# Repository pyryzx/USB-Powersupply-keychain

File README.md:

# Multi-Rail Power Supply Keychain (USB-C PD)

A compact, keychain-sized **USB-C powered** power supply that has four power rails:

- **+1.8 V** (up to 1.5 A)
- **+3.3 V** (up to 1.5 A)
- **+5 V** (up to 1.5 A)
- **+12 V (VBUS passthrough)** from the USB-C PD source

Clip this onto your keys, plug it into a USB-C PD charger, and you’ve got the most common lab voltages available from a single tiny board.

---

## Features

- USB-C input with **USB Power Delivery negotiation** (requests 12 V from a capable source)
- Multi-rail DC/DC conversion to generate **1.8 V, 3.3 V, and 5 V**
- **12 V VBUS rail is also available** as an output (source-dependent)
- Compact PCB with **keychain hole**

---

## Electrical Specs (Target)

> Real limits depend heavily on the USB-C PD source, total load, copper/thermal conditions, and airflow.

### Outputs

| Rail | Nominal Voltage | Max Current (design target) | Notes |
|---|---:|---:|---|
| +1.8V | 1.8 V | 1.5 A | Buck regulated |
| +3.3V | 3.3 V | 1.5 A | Buck regulated |
| +5V | 5.0 V | 1.5 A | Buck regulated |
| +12V | 12 V | Source-dependent | Direct from negotiated VBUS |

### Power Budget 

beware that even if each rail is “rated” for 1.5 A it is source dependent. 

Example (typical PD): **12 V × 3 A = 36 W available**  
Loads:
- 5 V @ 1.5 A ≈ 7.5 W  
- 3.3 V @ 1.5 A ≈ 5.0 W  
- 1.8 V @ 1.5 A ≈ 2.7 W  
Total ≈ 15.2 W (plus conversion losses)

Beware that current design is not yet optimized to be run at full capacity all the time. Heat generated is still a problem when run at max load.

## Output Connector / Pinout

### J3

Pin order (as labeled on schematic / silkscreen intent):

1. **+1.8V**
2. **+3.3V**
3. **+5V**
4. **+12V**
5. **GND**

---

## How It Works 

1. **USB-C input** comes in on the Type-C receptacle.
2. A **USB-C PD sink controller (CYPD3177-24LQ)** negotiates with the charger to request **12 V** output.
3. Once VBUS is valid, a small input switching/protection stage connects the negotiated rail to the board.
4. A **multi-output buck regulator (TPS65581PWP)** generates:
   - **1.8 V** (via L1)
   - **3.3 V** (via L2)
   - **5 V** (via L3)
5. The negotiated **+12 V VBUS** rail is also routed to the output header.

See: `schematic_keychain V2.pdf`. :contentReference[oaicite:1]{index=1}

---

## What This Is For

- Powering sensors, dev boards, and small embedded prototypes
- Quick “bench supply” substitute for field work
- Testing boards that need 1.8 V / 3.3 V / 5 V without dragging a lab PSU around

---

## What This Is NOT For

- Not a charger / power bank
- Not safety-certified equipment
- Not intended for life-critical, medical, automotive, or mains-related applications
- Not meant for inductive loads / motors directly 

---

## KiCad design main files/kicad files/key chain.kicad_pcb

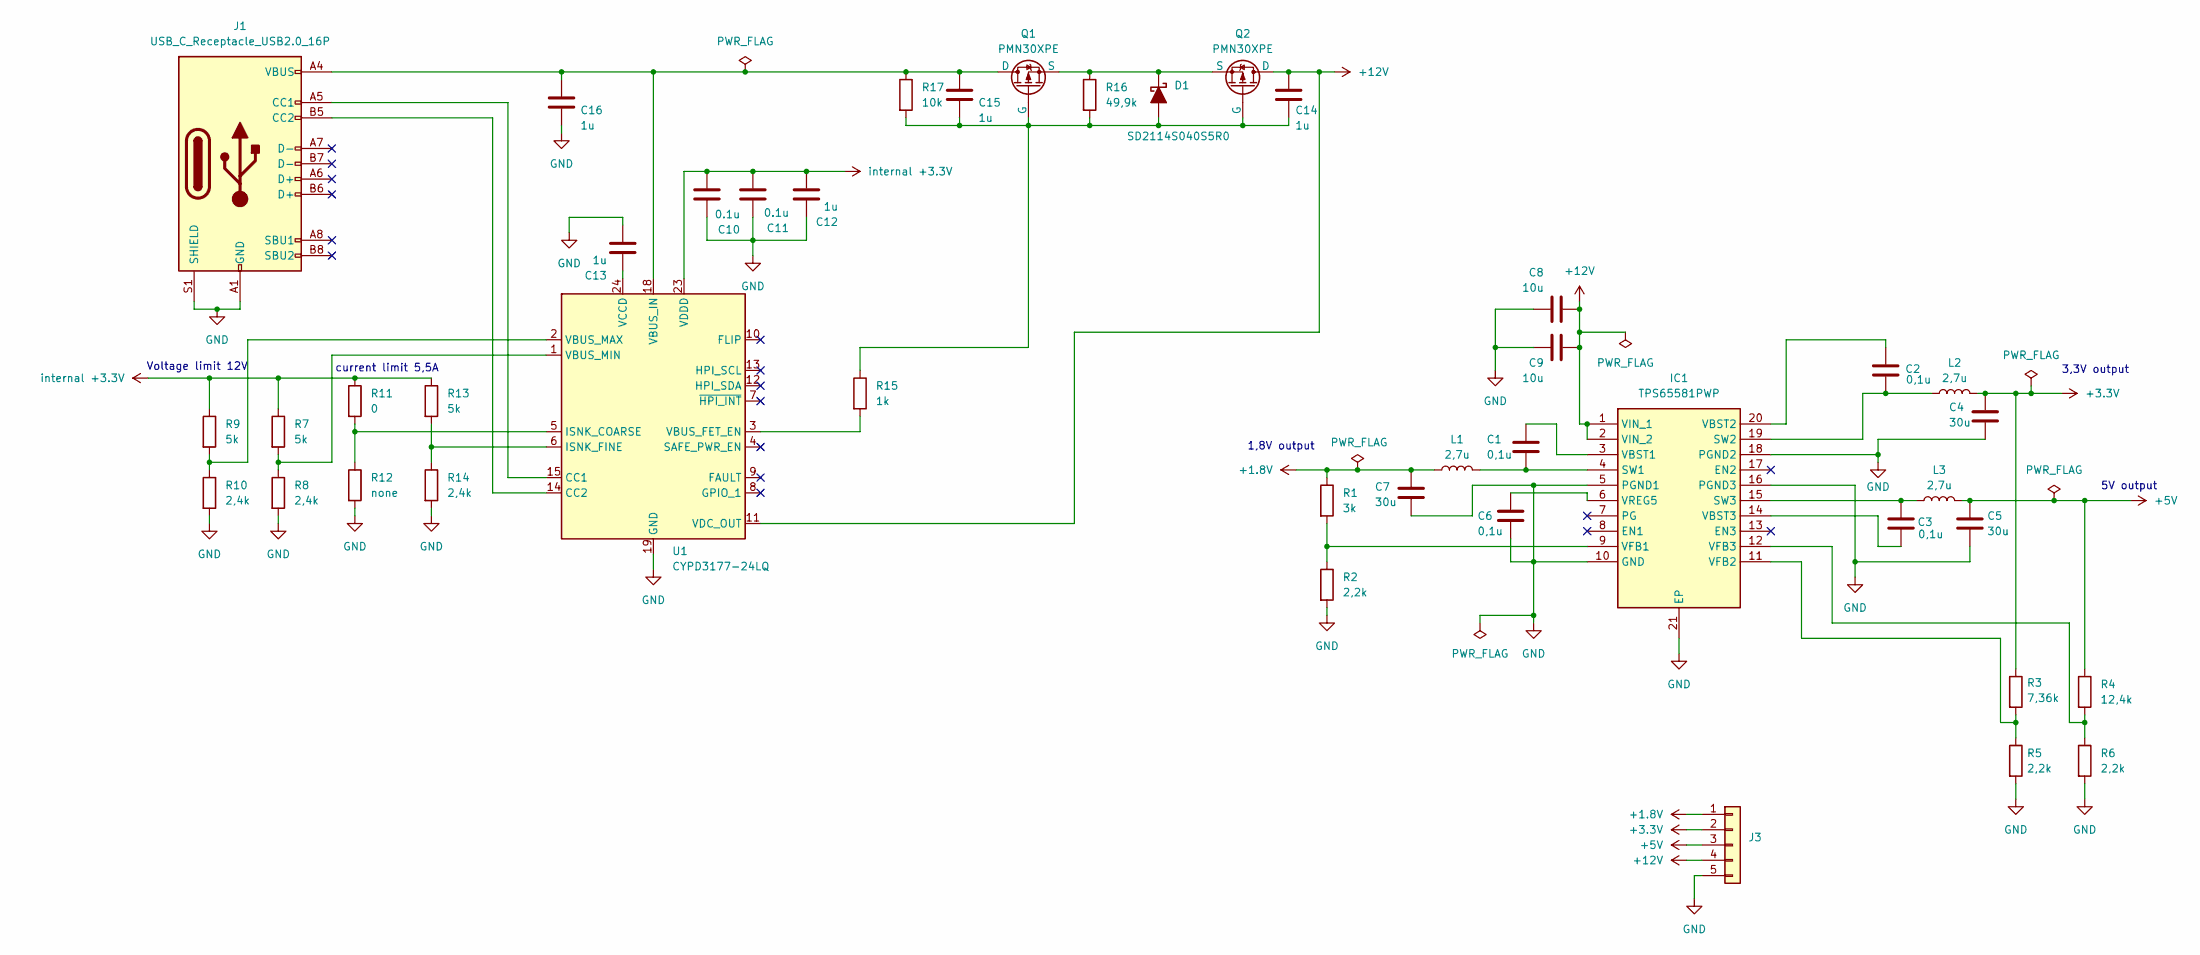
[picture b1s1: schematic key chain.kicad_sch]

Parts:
C1, C2, C3, C6: 0,1u; C_0603_1608Metric_Pad1.08x0.95mm_HandSolder
C4, C5, C7: 30u; C_0603_1608Metric_Pad1.08x0.95mm_HandSolder
C8, C9: 10u; C_0603_1608Metric_Pad1.08x0.95mm_HandSolder
C10, C11: 0.1u; C_0603_1608Metric_Pad1.08x0.95mm_HandSolder
C12, C13, C14, C15, C16: 1u; C_0603_1608Metric_Pad1.08x0.95mm_HandSolder
D1: SD2114S040S5R0
IC1: TPS65581PWP; SOP65P640X120-21N; Mouser Part Number 595-TPS65581PWP
J1: USB_C_Receptacle_USB2.0_16P; USB_C_Receptacle_HRO_TYPE-C-31-M-12
J3: Conn_01x05; PinSocket_1x05_P2.54mm_Vertical
L1, L2, L3: 2,7u; L_1812_4532Metric_Pad1.30x3.40mm_HandSolder
Q1, Q2: PMN30XPE; TSOP-6_1.65x3.05mm_P0.95mm
R1: 3k; R_0603_1608Metric_Pad0.98x0.95mm_HandSolder
R2, R5, R6: 2,2k; R_0603_1608Metric_Pad0.98x0.95mm_HandSolder
R3: 7,36k; R_0603_1608Metric_Pad0.98x0.95mm_HandSolder
R4: 12,4k; R_0603_1608Metric_Pad0.98x0.95mm_HandSolder
R7, R9, R13: 5k; R_0603_1608Metric_Pad0.98x0.95mm_HandSolder
R8, R10, R14: 2,4k; R_0603_1608Metric_Pad0.98x0.95mm_HandSolder
R11: 0; R_0603_1608Metric_Pad0.98x0.95mm_HandSolder
R12: none; R_0603_1608Metric_Pad0.98x0.95mm_HandSolder
R15: 1k; R_0603_1608Metric_Pad0.98x0.95mm_HandSolder
R16: 49,9k; R_0603_1608Metric_Pad0.98x0.95mm_HandSolder
R17: 10k; R_0603_1608Metric_Pad0.98x0.95mm_HandSolder
U1: CYPD3177-24LQ; QFN-24-1EP_4x4mm_P0.5mm_EP2.75x2.75mm

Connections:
+1.8V: C7.1, J3.1, L1.1, R1.1
+3.3V: C4.1, J3.2, L2.2, R3.1
+5V: C5.1, J3.3, L3.2, R4.1
+12V: C8.2, C9.2, C14.1, IC1.1 (VIN_1), IC1.2 (VIN_2), J3.4, Q2.1 (D), U1.11 (VDC_OUT)
GND: C4.2, C5.2, C6.2, C7.2, C8.1, C9.1, C10.1, C11.1, C12.1, C13.2, C16.2, IC1.5 (PGND1), IC1.10 (GND), IC1.16 (PGND3), IC1.18 (PGND2), IC1.21 (EP), J1.A1 (GND), J1.A12 (GND), J1.B1 (GND), J1.B12 (GND), J1.S1 (SHIELD), J3.5, R2.2, R5.2, R6.2, R8.2, R10.2, R12.2, R14.2, U1.19 (GND), U1.22 (GND), U1.25 (GND)
unnamed: C14.2, C15.2, D1.2 (A), Q1.2 (G), Q2.2 (G), R15.1, R16.2, R17.2
unnamed: D1.1 (K), Q1.3 (S), Q2.3 (S), R16.1
unnamed: C1.2, IC1.4 (SW1), L1.2
unnamed: C2.1, IC1.19 (SW2), L2.1
unnamed: C3.2, IC1.15 (SW3), L3.1
unnamed: C1.1, IC1.3 (VBST1)
unnamed: C2.2, IC1.20 (VBST2)
unnamed: C3.1, IC1.14 (VBST3)
unnamed: IC1.9 (VFB1), R1.2, R2.1
unnamed: IC1.11 (VFB2), R3.2, R5.1
unnamed: IC1.12 (VFB3), R4.2, R6.1
unnamed: C6.1, IC1.6 (VREG5)
unnamed: J1.A5 (CC1), U1.15 (CC1)
unnamed: J1.B5 (CC2), U1.14 (CC2)
unnamed: C15.1, C16.1, J1.A4 (VBUS), J1.A9 (VBUS), J1.B4 (VBUS), J1.B9 (VBUS), Q1.1 (D), R17.1, U1.18 (VBUS_IN)
unnamed: R11.2, R12.1, U1.5 (ISNK_COARSE)
unnamed: R13.2, R14.1, U1.6 (ISNK_FINE)
unnamed: R15.2, U1.3 (VBUS_FET_EN)
unnamed: R9.2, R10.1, U1.2 (VBUS_MAX)
unnamed: R7.2, R8.1, U1.1 (VBUS_MIN)
unnamed: C13.1, U1.24 (VCCD)
internal +3.3V: C10.2, C11.2, C12.2, R7.1, R9.1, R11.1, R13.1, U1.23 (VDDD)

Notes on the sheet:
1,8V output
current limit 5,5A
3,3V output
5V output
Voltage limit 12V

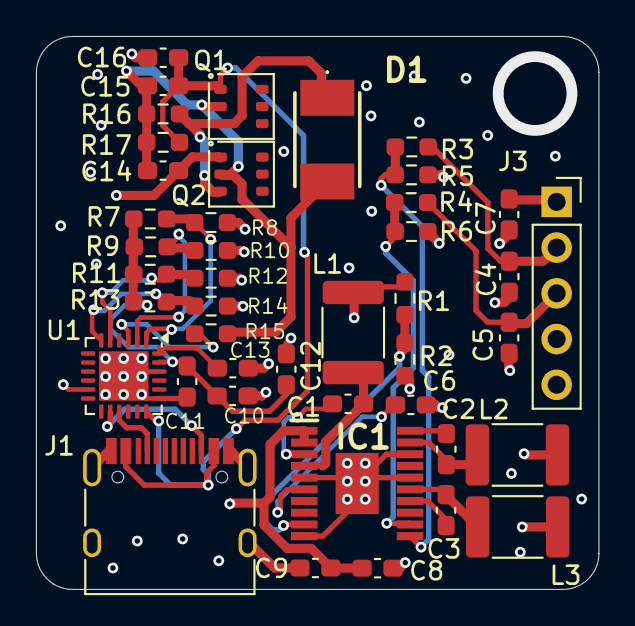
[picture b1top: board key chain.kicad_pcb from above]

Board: 4 copper layers, 31.2 x 30.7 mm, 43 parts (0 on the bottom side), 27 nets.

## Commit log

2026-01-13 added more detailed info to README
